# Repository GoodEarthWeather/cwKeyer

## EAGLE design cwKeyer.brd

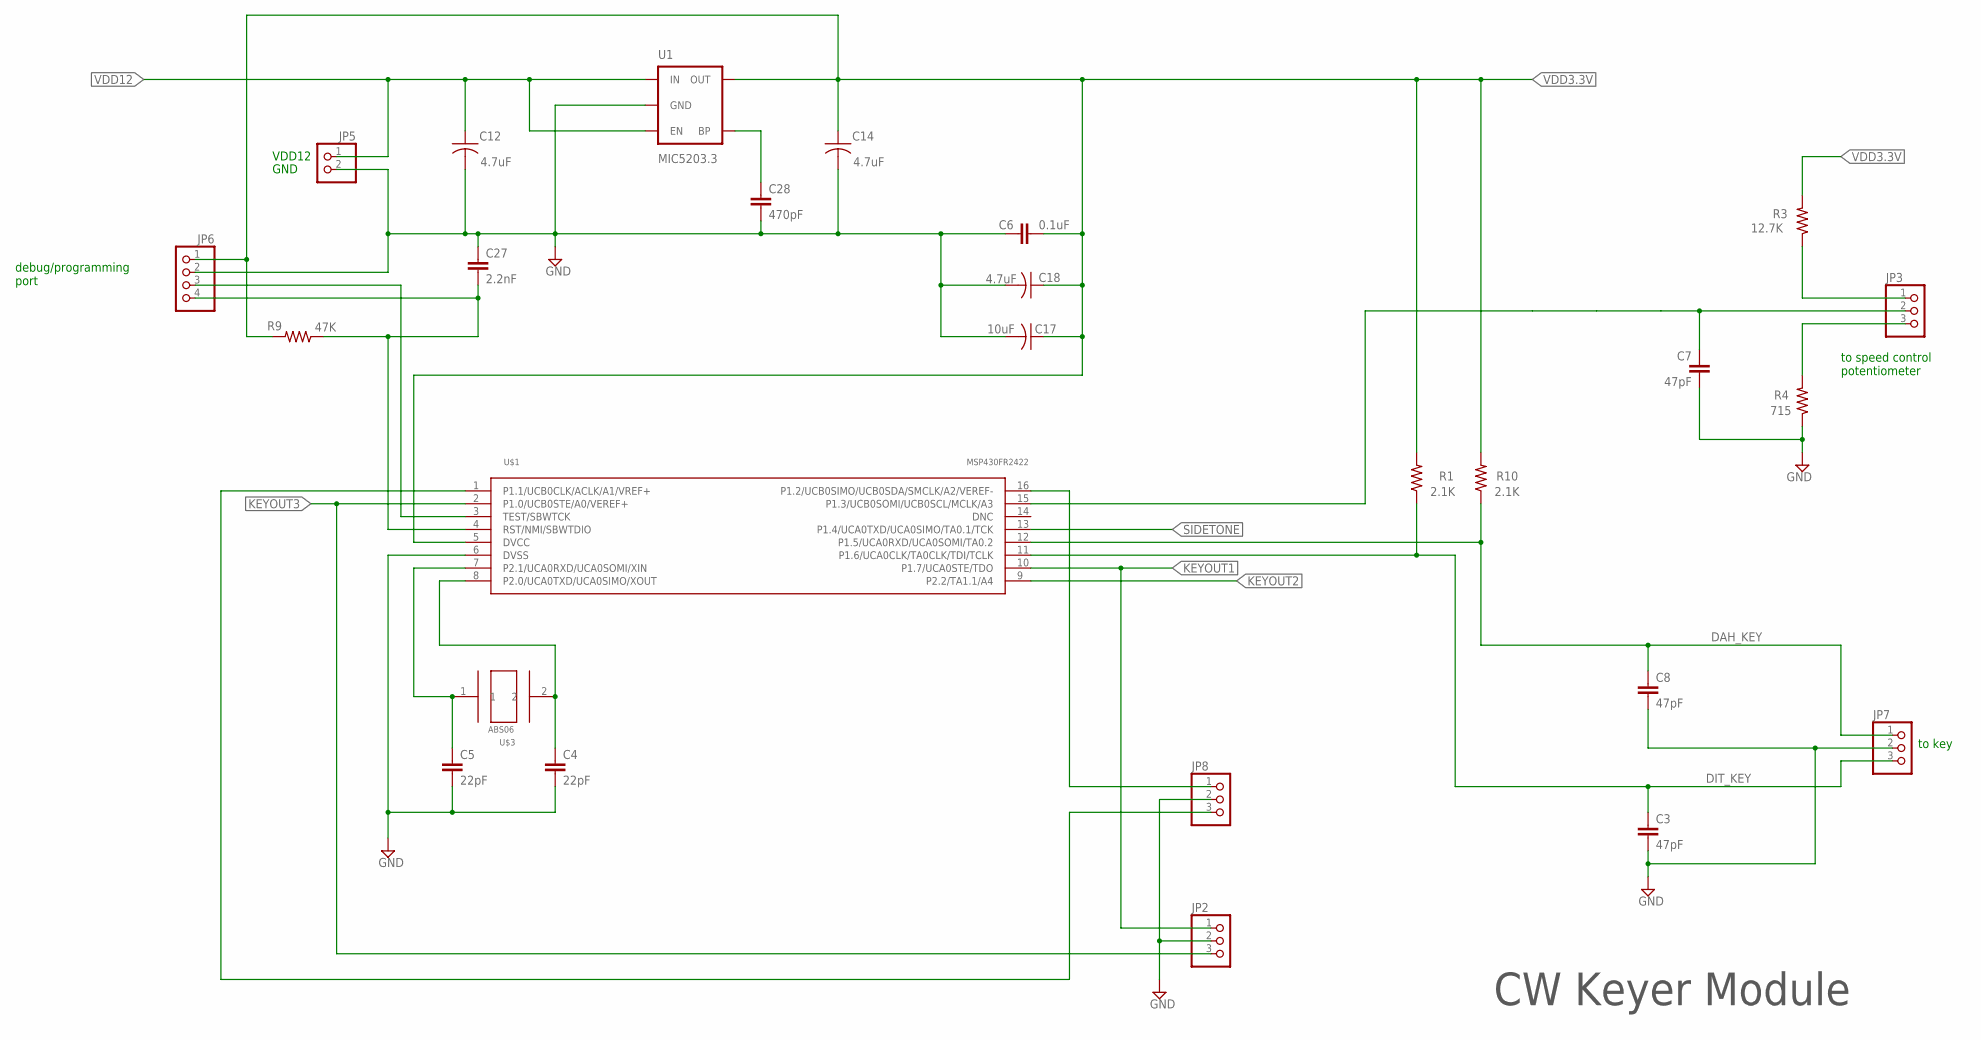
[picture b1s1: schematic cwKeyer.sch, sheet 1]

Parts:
C3, C7, C8: 47pF; 0603-CAP
C4, C5: 22pF; 0603-CAP
C6: 0.1uF; 0603-CAP
C12, C14, C18: 4.7uF; C0603
C17: 10uF; C0805
C27: 2.2nF; 0603-CAP
C28: 470pF; 0603-CAP
JP2, JP3, JP7, JP8: PINHD-1X3; 1X03
JP5: PINHD-1X2; 1X02
JP6: PINHD-1X4; 1X04
R1, R10: 2.1K; 0603-RES
R3: 12.7K; 0603-RES
R4: 715; 0603-RES
R9: 47K; 0603-RES
U1: MIC5203.3; SOT23-5
U$1: MSP430FR2422; TSSOP16
U$3: ABS06

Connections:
DAH_KEY: C8.1, JP7.1, R10.1, U$1.12 (P1.5/UCA0RXD/UCA0SOMI/TA0.2)
DIT_KEY: C3.1, JP7.3, R1.1, U$1.11 (P1.6/UCA0CLK/TA0CLK/TDI/TCLK)
GND: C3.2, C4.2, C5.2, C6.2, C7.2, C8.2, C12.2, C14.2, C17.2, C18.2, C27.1, C28.2, JP2.2, JP5.2, JP6.2, JP7.2, JP8.2, R4.1, U1.2 (GND), U$1.6 (DVSS); also elsewhere on the board
KEYOUT1: JP2.1, U$1.10 (P1.7/UCA0STE/TDO)
KEYOUT2: U$1.9 (P2.2/TA1.1/A4); also elsewhere on the board
KEYOUT3: JP2.3, U$1.2 (P1.0/UCB0STE/A0/VEREF+)
unnamed: C7.1, JP3.2, U$1.15 (P1.3/UCB0SOMI/UCB0SCL/MCLK/A3)
unnamed: C4.1, U$1.8 (P2.0/UCA0TXD/UCA0SIMO/XOUT), U$3.2
unnamed: JP3.3, R4.2
unnamed: JP3.1, R3.1
unnamed: C28.1, U1.4 (BP)
unnamed: JP6.3, U$1.3 (TEST/SBWTCK)
unnamed: C27.2, JP6.4, R9.1, U$1.4 (RST/NMI/SBWTDIO)
unnamed: C5.1, U$1.7 (P2.1/UCA0RXD/UCA0SOMI/XIN), U$3.1
unnamed: JP8.1, U$1.16 (P1.2/UCB0SIMO/UCB0SDA/SMCLK/A2/VEREF-)
unnamed: JP8.3, U$1.1 (P1.1/UCB0CLK/ACLK/A1/VREF+)
SIDETONE: U$1.13 (P1.4/UCA0TXD/UCA0SIMO/TA0.1/TCK); also elsewhere on the board
VDD3.3V: C6.1, C14.1, C17.1, C18.1, JP6.1, R1.2, R3.2, R9.2, R10.2, U1.5 (OUT), U$1.5 (DVCC)
VDD12: C12.1, JP5.1, U1.1 (IN), U1.3 (EN); also elsewhere on the board

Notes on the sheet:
CW Keyer Module
VDD12
debug/programming port
to key
to speed control potentiometer
GND

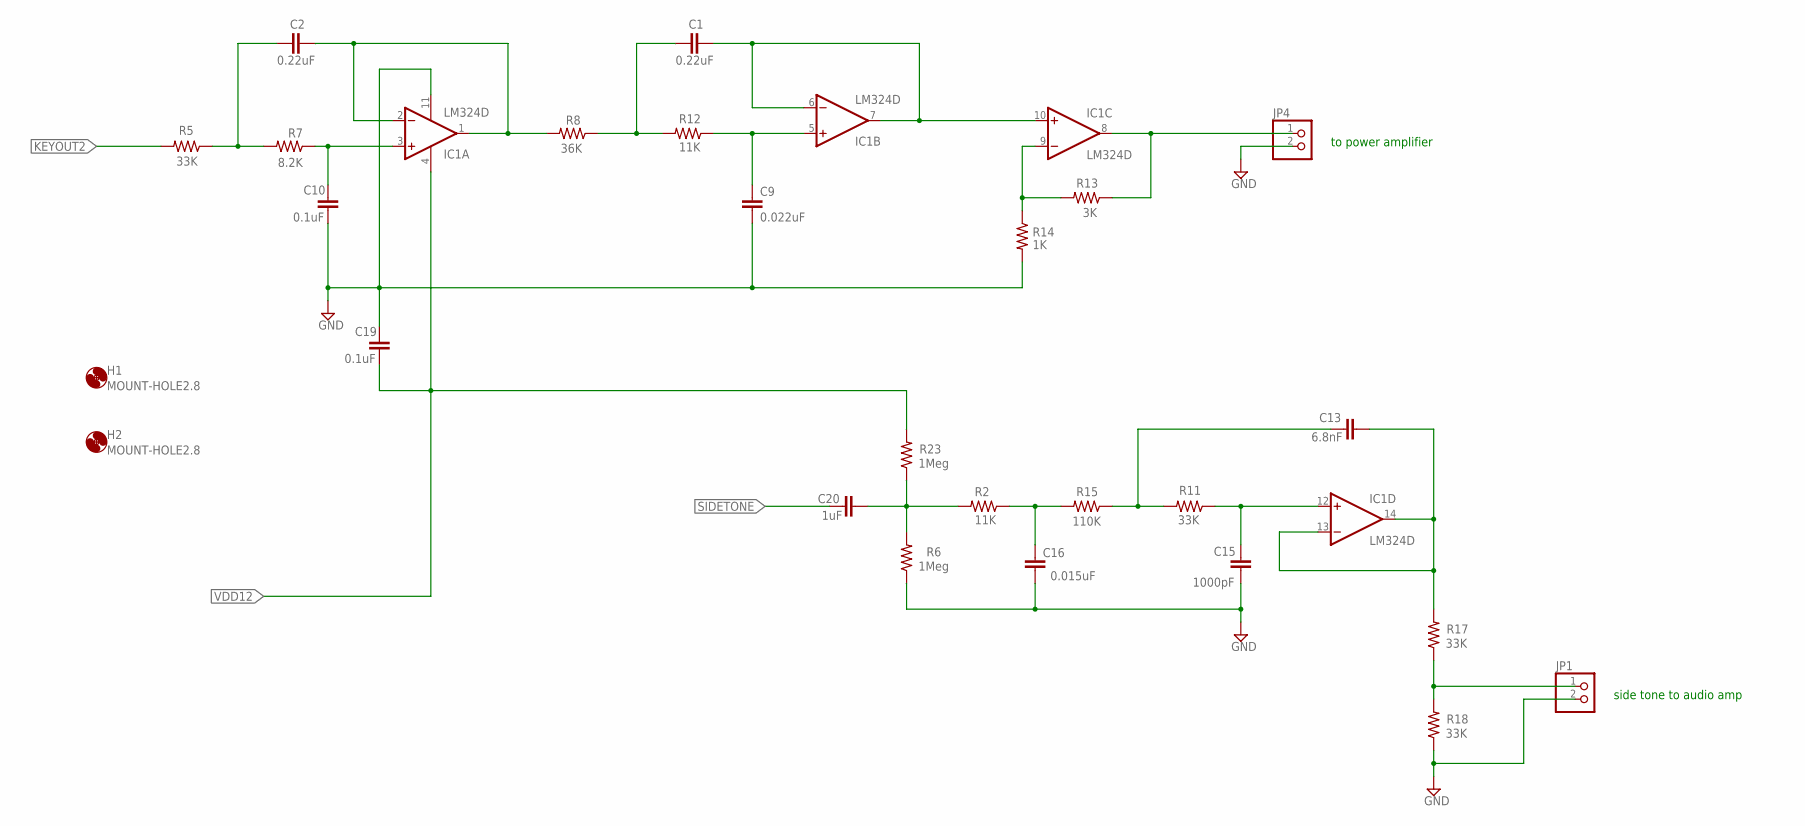
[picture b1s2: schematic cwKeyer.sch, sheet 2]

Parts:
C1, C2: 0.22uF; 0603-CAP
C9: 0.022uF; 0603-CAP
C10, C19: 0.1uF; 0603-CAP
C13: 6.8nF; 0603-CAP
C15: 1000pF; 0603-CAP
C16: 0.015uF; 0603-CAP
C20: 1uF; 0603-CAP
H1, H2: MOUNT-HOLE2.8; 2,8
IC1: LM324D; SO14
JP1, JP4: PINHD-1X2; 1X02
R2, R12: 11K; 0603-RES
R5, R11, R17, R18: 33K; 0603-RES
R6, R23: 1Meg; 0603-RES
R7: 8.2K; 0603-RES
R8: 36K; 0603-RES
R13: 3K; 0603-RES
R14: 1K; 0603-RES
R15: 110K; 0603-RES

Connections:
GND: C9.2, C10.2, C15.1, C16.1, C19.1, IC1.11 (V-), JP1.2, JP4.2, R6.1, R14.2, R18.1; also elsewhere on the board
KEYOUT2: R5.2; also elsewhere on the board
unnamed: JP1.1, R17.1, R18.2
unnamed: IC1.8 (OUT), JP4.1, R13.1
unnamed: C13.2, IC1.13 (-IN), IC1.14 (OUT), R17.2
unnamed: C20.2, R2.2, R6.2, R23.1
unnamed: C10.1, IC1.3 (+IN), R7.1
unnamed: C2.1, R5.1, R7.2
unnamed: C15.2, IC1.12 (+IN), R11.1
unnamed: C2.2, IC1.1 (OUT), IC1.2 (-IN), R8.2
unnamed: C1.1, R8.1, R12.2
unnamed: C9.1, IC1.5 (+IN), R12.1
unnamed: C13.1, R11.2, R15.1
unnamed: C16.2, R2.1, R15.2
unnamed: C1.2, IC1.6 (-IN), IC1.7 (OUT), IC1.10 (+IN)
unnamed: IC1.9 (-IN), R13.2, R14.1
SIDETONE: C20.1; also elsewhere on the board
VDD12: C19.2, IC1.4 (V+), R23.2; also elsewhere on the board

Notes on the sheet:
to power amplifier
side tone to audio amp

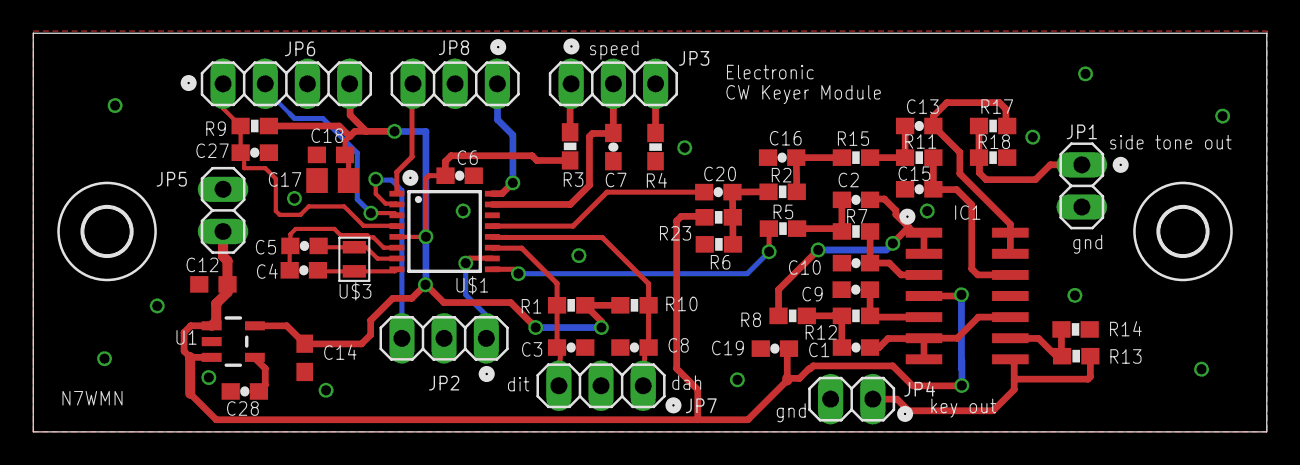
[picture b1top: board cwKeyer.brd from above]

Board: 2 copper layers, 74.3 x 24.0 mm, 53 parts (0 on the bottom side), 33 nets.

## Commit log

2018-12-09 ignore files
2019-01-17 untrack object files
2022-01-23 enabled key port functionality
2022-01-23 initial
2022-01-23 removed old driver lib
2022-02-10 Create test
2022-02-10 Add files via upload
    adding schematic and board files
2025-10-29 First commit from rebuilt project on Linux
2025-10-29 Changed location of repo to be outside of CCS workspace

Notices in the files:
parts and their libraries:
SparkFun-Passives: Licensing: Creative Commons ShareAlike 4.0 International - https://creativecommons.org/licenses/by-sa/4.0
